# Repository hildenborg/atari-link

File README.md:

## About
The purpose of Atari-Link is to give developers using [m68k-atari-dev toolchain](https://github.com/hildenborg/m68k-atari-dev) the possibillity of developing for real Atari computers the same way they are used to target the Hatari emulator.  
If you aren't a developer and only want a ACSI SD-Card hard disk emulator, then there are many other options with better support.  
The [wiki](https://github.com/hildenborg/atari-link/wiki) is recommended for deeper information  

## Hardware
The hardware is designed in KiCad and the project can be found in the "kicad" directory.  
It is designed to be "easy" to build by hand, and the wiki have more information about that.

## Firmware
The hardware is based around the Raspberry Pico and the formware source is in the "firmware" directory.  
The project is dependent on a submodule, so do not forget to do `git submodule init` and `git submodule update` after cloning this git repository.  

## Setup
If you have built the hardware, and just want to get going, then download [atari-link.zip](https://github.com/hildenborg/atari-link/releases/download/Release1_1/atari_link.zip) and extract its contents.  
Flash the Pico with "atari_link.uf2" and put "config.txt, "tos32mb_ahdi5_boot.img" and "tos32mb_gdbsrv.img" on a FAT32 formatted SD-card.  
This will set you up with a development system that should work on pretty much anything Atari have made.  
You may need to edit the "config.txt" file if you have other hard drives connected, so there aren't any device id collision.  
The hard disk images in the release is TOS 32MB formatted images so they should work on just about anything.  
The "config.txt" in the release is set up so the "tos32mb_ahdi5_boot.img" disk image is not seen by the PC and the "tos32mb_gdbsrv.img" is read-only by the Atari. The "tos32mb_gdbsrv.img" is visible on the PC as a USB drive and files written to it are immediately accessible on the Atari.  
NOTE: Even TOS formatted hard disk images are accessible to the PC as a USB drive. There's a [wiki page](https://github.com/hildenborg/atari-link/wiki/ProblemsSolutions) that describes how it works.

## Usage
The "extras" directory contains a "hello world" example using VsCode and Atari-Link with m68k-atari-dev toolchain.  
This example works exactly the same as the "vscode_hatari" example in the m68k-atari-dev examples.  
After having set up your Atari-Link with firmware and a SD-Card with the released images, you should now be able to start your atari and have a C and D drive (you may have to install the D drive).  
The D drive is the drive that appears as a USB drive on your PC. This is specified in the "config.txt" file that came with the disk images.  
On the D drive there is "gdbsrv.ttp" which you start with "--multi hello.prg" arguments.  
On your PC, execute "./vscode.sh" and in VsCode, press "Shoft-Ctrl-B" to build and "F5" to execute on your atari.  

## License:
This project is MIT licensed.  
The submodule: [no-OS-FatFS-SD-SPI-RPi-Pico](https://github.com/carlk3/no-OS-FatFS-SD-SPI-RPi-Pico) is a separate project and is Apache-2.0 licensed.

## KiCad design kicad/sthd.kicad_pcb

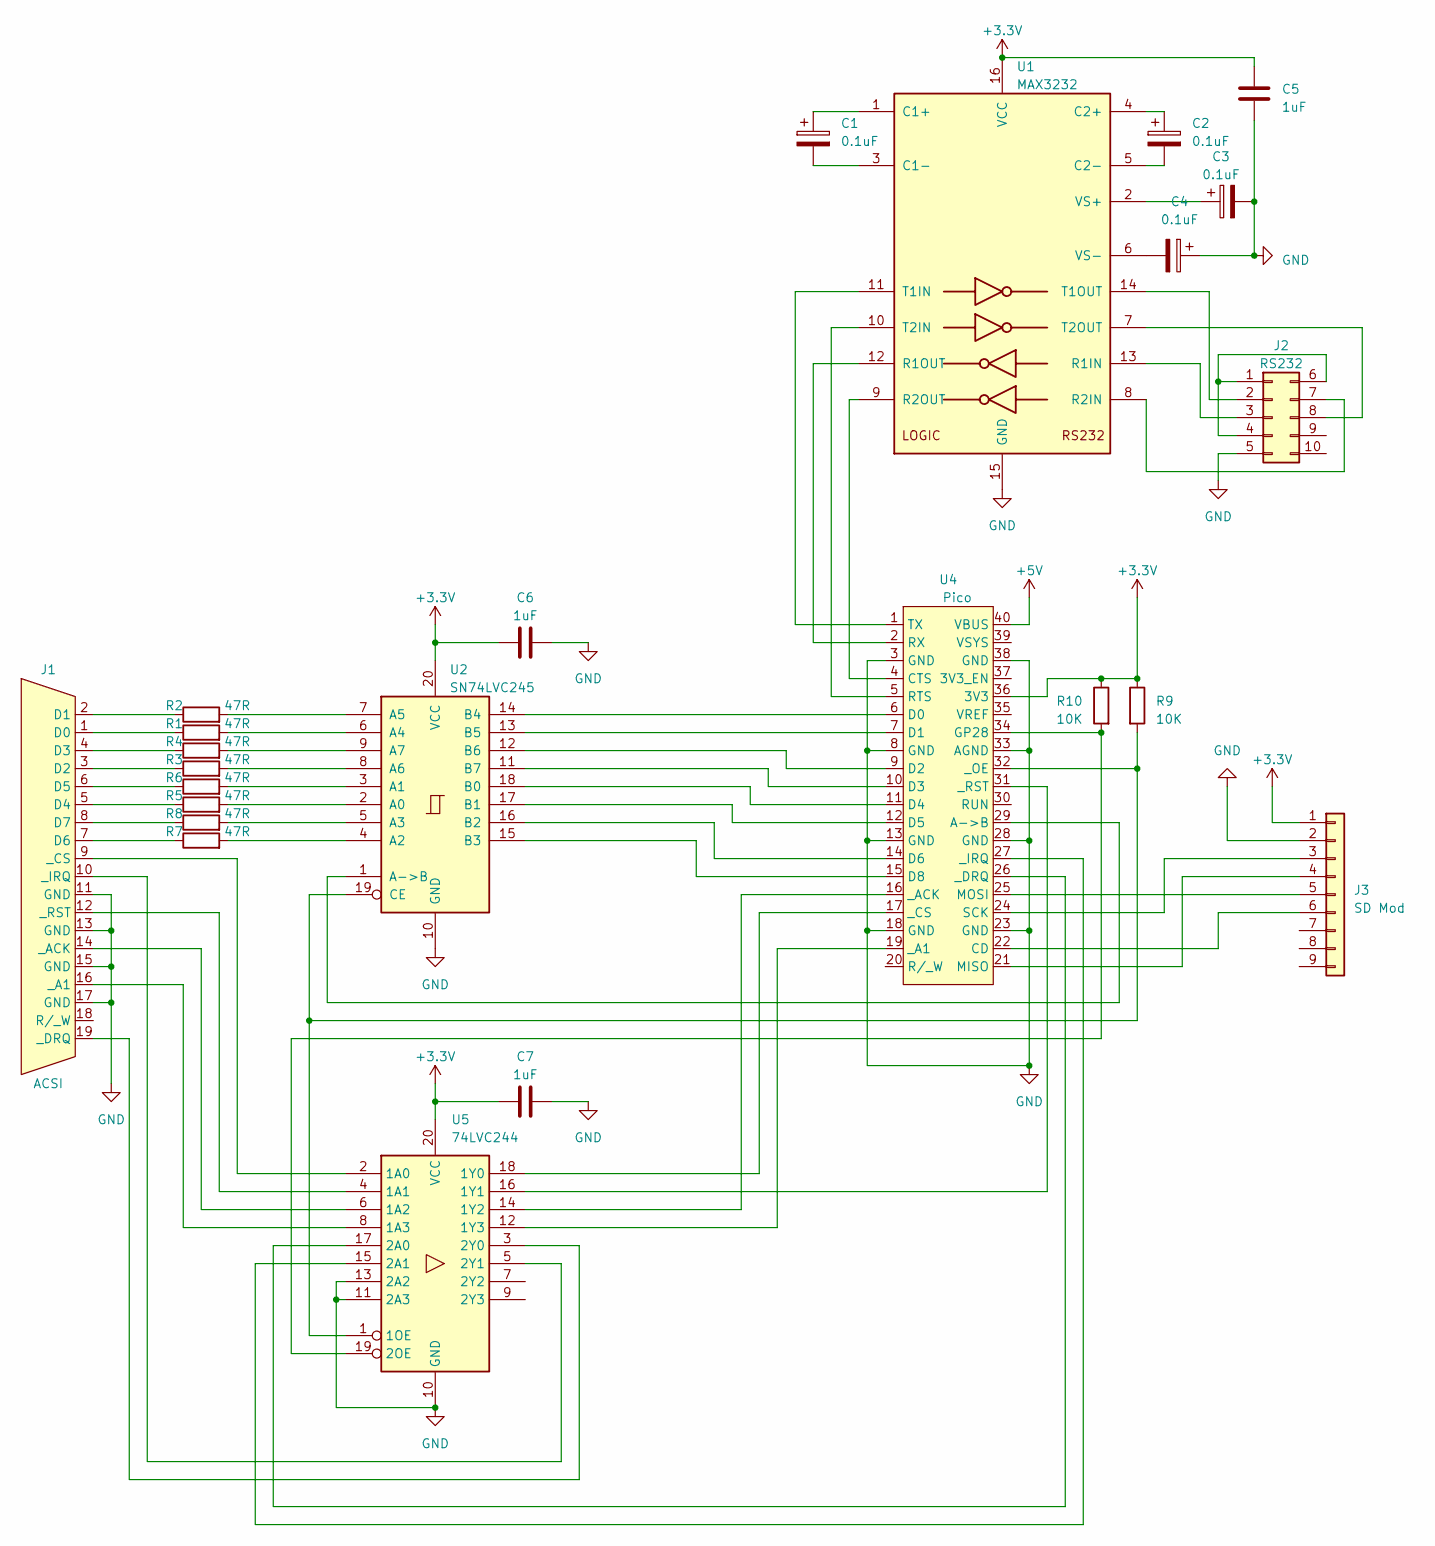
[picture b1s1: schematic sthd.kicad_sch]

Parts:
C1, C2, C3, C4: 0.1uF; CP_Radial_D5.0mm_P2.00mm
C5, C6, C7: 1uF; C_Disc_D5.0mm_W2.5mm_P5.00mm
J1: ACSI; DB19
J2: RS232; IDC-Header_2x05_P2.54mm_Vertical
J3: SD Mod; PinHeader_1x09_P2.54mm_Vertical
R1, R2, R3, R4, R5, R6, R7, R8: 47R; R_Axial_DIN0207_L6.3mm_D2.5mm_P10.16mm_Horizontal
R9, R10: 10K; R_Axial_DIN0207_L6.3mm_D2.5mm_P10.16mm_Horizontal
U1: MAX3232; DIP-16_W7.62mm
U2: SN74LVC245; DIP-20_W7.62mm
U4: Pico
U5: 74LVC244; DIP-20_W7.62mm

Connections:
+3.3V: C5.1, C6.1, C7.1, J3.1, R9.1, R10.1, U1.16 (VCC), U2.20 (VCC), U4.36 (3V3), U5.20 (VCC)
+5V: U4.40 (VBUS)
GND: C3.2, C4.1, C5.2, C6.2, C7.2, J1.11 (GND), J1.13 (GND), J1.15 (GND), J1.17 (GND), J2.5, J3.2, U1.15 (GND), U2.10 (GND), U4.3 (GND), U4.8 (GND), U4.13 (GND), U4.18 (GND), U4.23 (GND), U4.28 (GND), U4.33 (AGND), U4.38 (GND), U5.10 (GND), U5.11 (2A3), U5.13 (2A2)
unnamed: J1.1 (D0), R1.1
unnamed: J1.2 (D1), R2.1
unnamed: J1.3 (D2), R3.1
unnamed: J1.4 (D3), R4.1
unnamed: J1.5 (D4), R5.1
unnamed: J1.6 (D5), R6.1
unnamed: J1.7 (D6), R7.1
unnamed: J1.8 (D7), R8.1
unnamed: J1.16 (_A1), U5.8 (1A3)
unnamed: J1.14 (_ACK), U5.6 (1A2)
unnamed: J1.9 (_CS), U5.2 (1A0)
unnamed: J1.19 (_DRQ), U5.3 (2Y0)
unnamed: J1.10 (_IRQ), U5.5 (2Y1)
unnamed: J1.12 (_RST), U5.4 (1A1)
unnamed: J2.1, J2.4, J2.6
unnamed: J2.2, U1.14 (T1OUT)
unnamed: J2.3, U1.13 (R1IN)
unnamed: J2.7, U1.8 (R2IN)
unnamed: J2.8, U1.7 (T2OUT)
unnamed: J3.3, U4.24 (SCK)
unnamed: J3.4, U4.21 (MISO)
unnamed: J3.5, U4.25 (MOSI)
unnamed: J3.6, U4.22 (CD)
unnamed: C1.1, U1.1 (C1+)
unnamed: C1.2, U1.3 (C1-)
unnamed: C2.1, U1.4 (C2+)
unnamed: C2.2, U1.5 (C2-)
unnamed: U1.12 (R1OUT), U4.2 (RX)
unnamed: U1.9 (R2OUT), U4.4 (CTS)
unnamed: U1.11 (T1IN), U4.1 (TX)
unnamed: U1.10 (T2IN), U4.5 (RTS)
unnamed: C3.1, U1.2 (VS+)
unnamed: C4.2, U1.6 (VS-)
unnamed: R5.2, U2.2 (A0)
unnamed: R6.2, U2.3 (A1)
unnamed: R7.2, U2.4 (A2)
unnamed: R8.2, U2.5 (A3)
unnamed: R1.2, U2.6 (A4)
unnamed: R2.2, U2.7 (A5)
unnamed: R3.2, U2.8 (A6)
unnamed: R4.2, U2.9 (A7)
unnamed: U2.1 (A->B), U4.29 (A->B)
unnamed: U2.18 (B0), U4.11 (D4)
unnamed: U2.17 (B1), U4.12 (D5)
unnamed: U2.16 (B2), U4.14 (D6)
unnamed: U2.15 (B3), U4.15 (D8)
unnamed: U2.14 (B4), U4.6 (D0)
unnamed: U2.13 (B5), U4.7 (D1)
unnamed: U2.12 (B6), U4.9 (D2)
unnamed: U2.11 (B7), U4.10 (D3)
unnamed: R9.2, U2.19 (CE), U4.32 (_OE), U5.1 (1OE)
unnamed: R10.2, U4.34 (GP28), U5.19 (2OE)
unnamed: U4.19 (_A1), U5.12 (1Y3)
unnamed: U4.16 (_ACK), U5.14 (1Y2)
unnamed: U4.17 (_CS), U5.18 (1Y0)
unnamed: U4.26 (_DRQ), U5.17 (2A0)
unnamed: U4.27 (_IRQ), U5.15 (2A1)
unnamed: U4.31 (_RST), U5.16 (1Y1)

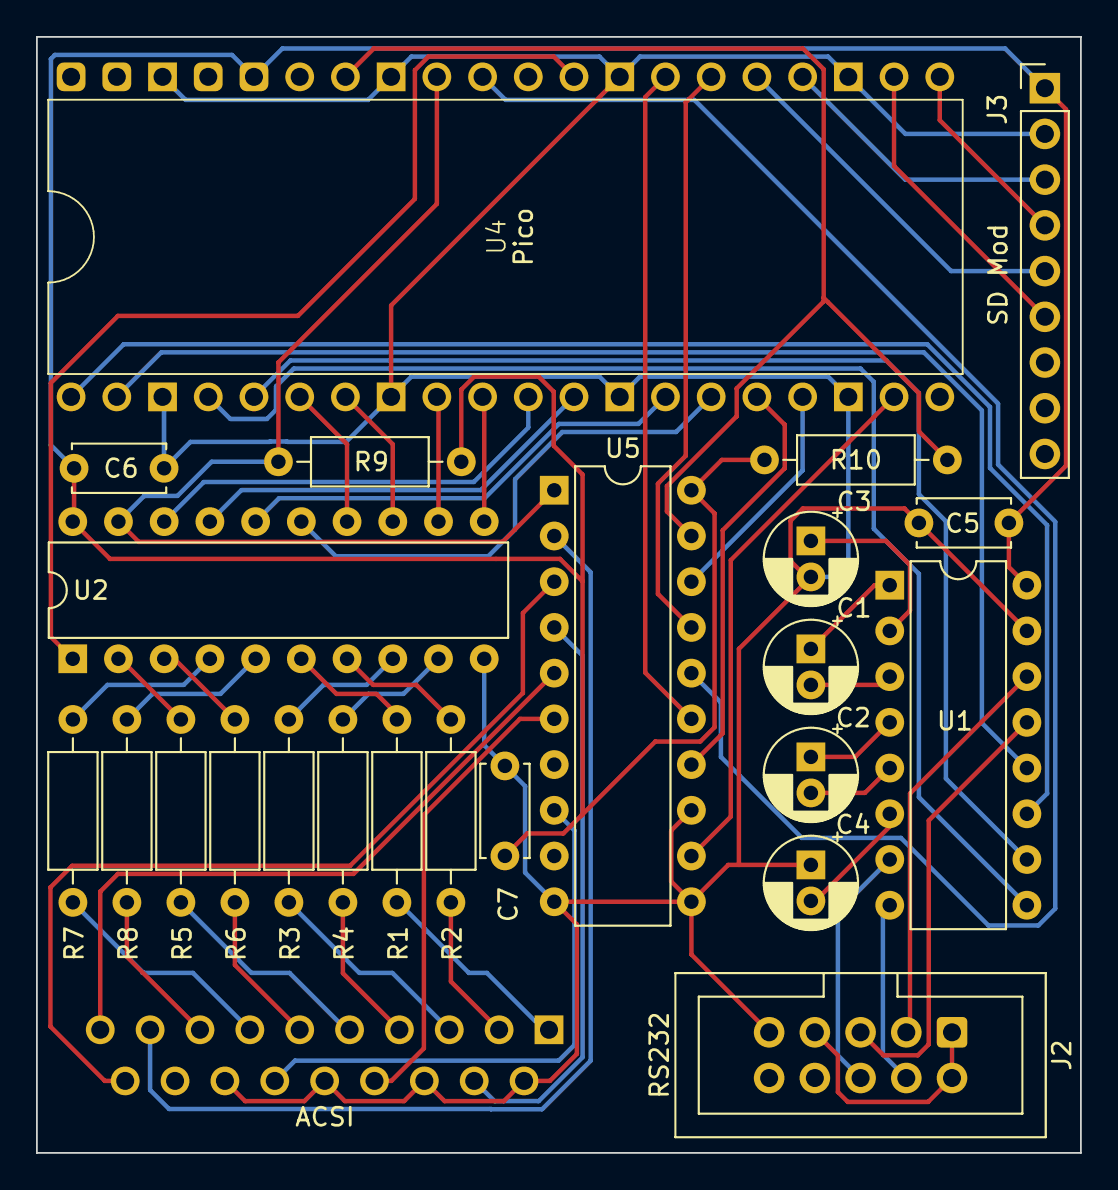
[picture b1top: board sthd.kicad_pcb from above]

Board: 2 copper layers, 58.0 x 62.0 mm, 24 parts (1 on the bottom side), 60 nets.

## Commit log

2026-06-04 setting up repo
2026-06-04 redoing submodules
2026-06-04 submodule license
2026-06-04 removed headline
2026-06-07 Updated project settings.
2026-06-10 Correct setting of oe1 and oe2 when startup or reset.
2026-06-10 documenting
2026-06-16 Fixed bug where ACSI emulation randomly would not start after power off and on.
2026-06-19 fixed release link
2026-06-21 hello world
